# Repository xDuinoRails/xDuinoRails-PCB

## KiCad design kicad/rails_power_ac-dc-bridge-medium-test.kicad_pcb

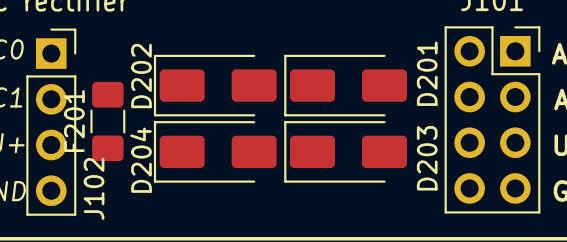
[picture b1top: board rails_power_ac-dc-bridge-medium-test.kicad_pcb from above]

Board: 2 copper layers, 7 parts (0 on the bottom side), 5 nets, no tracks yet.

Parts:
D201, D202, D203, D204: SS14; D_SMA
F201: SRF1206P150; Fuse_1206_3216Metric_Pad1.42x1.75mm_HandSolder
J101: Conn_02x04_Odd_Even; PinSocket_2x04_P2.54mm_Vertical
J102: Conn_01x04; PinSocket_1x04_P2.54mm_Vertical

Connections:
/J_AC0: D201.1 (K), D202.2 (A), J101.1, J101.2, J102.1
/J_AC1: D203.1 (K), D204.2 (A), J101.3, J101.4, J102.2
/J_GND: D201.2 (A), D203.2 (A), J101.8, J102.4
/J_U+: F201.2, J101.6, J102.3
/rails_power_ac-dc-bridge-medium/+U_UNFUSED: D202.1 (K), D204.1 (K), F201.1

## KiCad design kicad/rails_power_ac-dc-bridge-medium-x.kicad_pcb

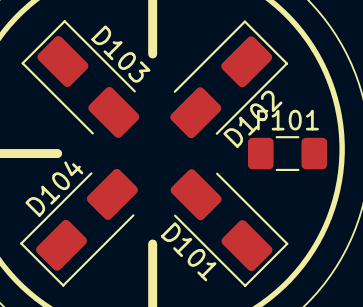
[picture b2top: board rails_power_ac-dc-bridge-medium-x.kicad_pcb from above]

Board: 2 copper layers, 5 parts (0 on the bottom side), 4 nets, no tracks yet.

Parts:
D101, D102, D103, D104: SS14; D_SMA
F101: SRF1206P150; Fuse_1206_3216Metric_Pad1.42x1.75mm_HandSolder

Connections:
/+U_UNFUSED: D102.1 (K), D104.1 (K), F101.1
/AC0: D101.1 (K), D102.2 (A)
/AC1: D103.1 (K), D104.2 (A)
/GND: D101.2 (A), D103.2 (A)

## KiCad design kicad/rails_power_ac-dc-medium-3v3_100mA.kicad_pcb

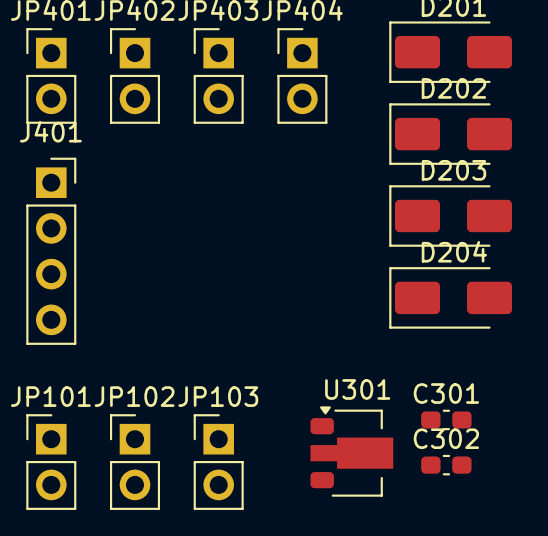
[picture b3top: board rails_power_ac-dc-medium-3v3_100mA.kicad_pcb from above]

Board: 2 copper layers, 15 parts (0 on the bottom side), 7 nets, no tracks yet.

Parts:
C301: 1u; C_0603_1608Metric_Pad1.08x0.95mm_HandSolder
C302: 47uF; C_0603_1608Metric_Pad1.08x0.95mm_HandSolder
D201, D202, D203, D204: SS14; D_SMA
J401: Conn_01x04; PinSocket_1x04_P2.54mm_Vertical
JP101, JP102, JP103, JP401, JP402, JP403, JP404: Jumper_2_Bridged; PinHeader_1x02_P2.54mm_Vertical
U301: HT75xx-1-SOT89; SOT-89-3

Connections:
+3V3: C302.1, JP101.2 (B), U301.3 (VOUT)
+U: C301.1, JP102.1 (A), JP102.2 (B), JP403.1 (A), U301.2 (VIN)
/rails_power_ac-dc-bridge-medium-test/J_AC0: D201.1 (K), D202.2 (A), J401.1, JP401.2 (B)
/rails_power_ac-dc-bridge-medium-test/J_AC1: D203.1 (K), D204.2 (A), J401.2, JP402.2 (B)
/rails_power_ac-dc-bridge-medium-test/J_GND: D201.2 (A), D203.2 (A), J401.4, JP404.2 (B)
/rails_power_ac-dc-bridge-medium-test/J_U+: D202.1 (K), D204.1 (K), J401.3, JP403.2 (B)
GND: C301.2, C302.2, JP103.1 (A), JP103.2 (B), JP404.1 (A), U301.1 (GND)

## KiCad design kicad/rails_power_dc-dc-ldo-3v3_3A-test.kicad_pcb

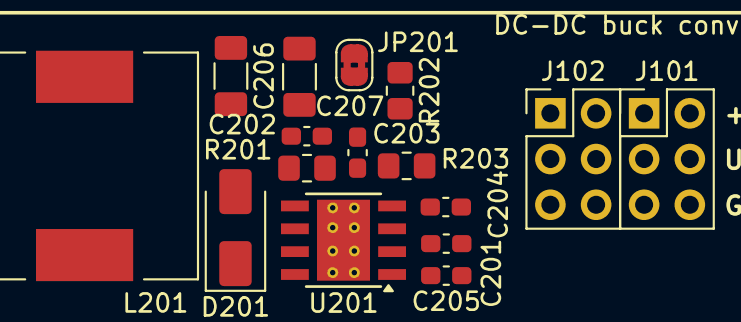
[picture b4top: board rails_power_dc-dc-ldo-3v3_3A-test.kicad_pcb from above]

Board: 2 copper layers, 16 parts (0 on the bottom side), 10 nets, no tracks yet.

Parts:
C201: 1u; C_0603_1608Metric_Pad1.08x0.95mm_HandSolder
C202: 10pF; C_0603_1608Metric_Pad1.08x0.95mm_HandSolder
C203: 1nF; C_0603_1608Metric_Pad1.08x0.95mm_HandSolder
C204, C205: 10nF; C_0603_1608Metric_Pad1.08x0.95mm_HandSolder
C206, C207: 100uF; C_1206_3216Metric_Pad1.33x1.80mm_HandSolder
D201: D_Schottky; D_SMA
J101, J102: Conn_02x03_Odd_Even; PinHeader_2x03_P2.54mm_Vertical
JP201: SolderJumper_2_Bridged; SolderJumper-2_P1.3mm_Bridged2Bar_RoundedPad1.0x1.5mm
L201: L; L_12x12mm_H4.5mm
R201, R202, R203: R; R_0805_2012Metric_Pad1.20x1.40mm_HandSolder
U201: TPS54233; TI_SO-PowerPAD-8_ThermalVias

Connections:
/J_+3V3: J101.3, J102.3, J102.4, JP201.2 (B), R202.1
/J_GND: C201.2, C202.2, C203.2, C204.2, C206.2, C207.2, D201.2 (A), J101.5, J102.5, J102.6, R203.2, U201.7 (GND)
/J_U+: C201.1, J101.1, J102.1, J102.2, U201.2 (VIN)
/rails_power_dc-dc-ldo-3v3_3A/BOOT: C205.1, U201.1 (BOOT)
/rails_power_dc-dc-ldo-3v3_3A/COMP: C202.1, R201.2, U201.6 (COMP)
/rails_power_dc-dc-ldo-3v3_3A/FEEDBACK: R202.2, R203.1, U201.5 (FB)
/rails_power_dc-dc-ldo-3v3_3A/PH: C205.2, D201.1 (K), L201.1, U201.8 (PH)
/rails_power_dc-dc-ldo-3v3_3A/SS: C204.1, U201.4 (SS)
unnamed: C203.1, R201.1
unnamed: C206.1, C207.1, JP201.1 (A), L201.2

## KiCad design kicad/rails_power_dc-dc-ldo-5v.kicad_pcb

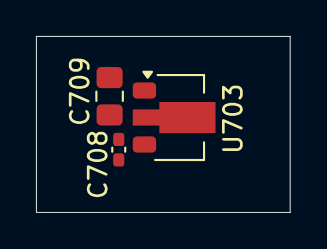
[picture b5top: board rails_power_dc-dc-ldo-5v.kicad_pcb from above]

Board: 2 copper layers, 14.1 x 9.8 mm, 3 parts (0 on the bottom side), 3 nets, no tracks yet.

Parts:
C708: 1uF; C_0402_1005Metric_Pad0.74x0.62mm_HandSolder
C709: 47uF; C_0805_2012Metric_Pad1.18x1.45mm_HandSolder
U703: L78L05_SOT89; SOT-89-3

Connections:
/+5V: C709.1, U703.1 (OUT)
GND: C708.2, C709.2, U703.2 (GND)
unnamed: C708.1, U703.3 (IN)

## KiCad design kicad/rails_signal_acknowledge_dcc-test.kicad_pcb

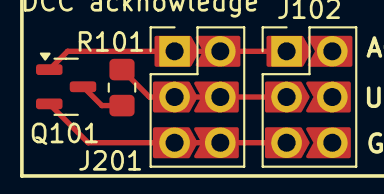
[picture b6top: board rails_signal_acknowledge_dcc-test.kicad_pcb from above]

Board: 2 copper layers, 4 parts (0 on the bottom side), 4 nets.

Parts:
J102, J201: Conn_02x03_Odd_Even; PinHeaderJP_2x03_P2.54mm_Vertical
Q101: S8050; 8x50_SOT-23
R101: 150R; R_0805_2012Metric_Pad1.20x1.40mm_HandSolder

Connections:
0: J102.5, J201.5, J201.6, Q101.1 (E)
/J_DCC_ACK: J102.1, J201.1, J201.2, Q101.2 (B)
/J_U+: J102.3, J201.3, J201.4, R101.2
/rails-signal-acknowledge_dcc/U+_DROP: Q101.3 (C), R101.1
